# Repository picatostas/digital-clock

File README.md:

# digital-clock
Eagle files for my TTL-CMOS digital clock

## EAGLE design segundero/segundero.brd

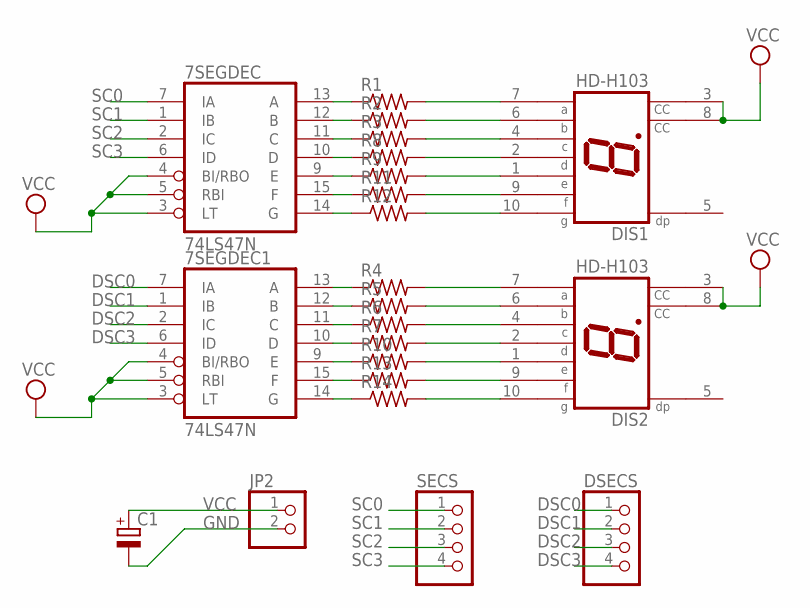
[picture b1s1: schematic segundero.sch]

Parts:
7SEGDEC, 7SEGDEC1: 74LS47N; DIL16
C1: CPOL-EUE2-5; E2-5
DIS1, DIS2: HD-H103; HDSP-M
DSECS: PINHD-1X4; 1X04
JP2: PINHD-1X2; 1X02
R1, R2, R3, R4, R5, R6, R7, R8, R9, R10, R11, R12, R13, R14: R-US_0204/7; 0204/7
SECS: PINHD-1X4; 1X04

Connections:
DSC0: 7SEGDEC1.7 (IA), DSECS.1
DSC1: 7SEGDEC1.1 (IB), DSECS.2
DSC2: 7SEGDEC1.2 (IC), DSECS.3
DSC3: 7SEGDEC1.6 (ID), DSECS.4
GND: 7SEGDEC.8 (GND), 7SEGDEC1.8 (GND), C1.-, JP2.2
unnamed: 7SEGDEC1.15 (F), R13.1
unnamed: 7SEGDEC1.13 (A), R4.1
unnamed: 7SEGDEC.15 (F), R11.1
unnamed: 7SEGDEC1.12 (B), R5.1
unnamed: 7SEGDEC.13 (A), R1.1
unnamed: 7SEGDEC1.11 (C), R6.1
unnamed: 7SEGDEC1.10 (D), R7.1
unnamed: 7SEGDEC1.9 (E), R10.1
unnamed: 7SEGDEC.12 (B), R2.1
unnamed: 7SEGDEC.11 (C), R3.1
unnamed: 7SEGDEC.10 (D), R8.1
unnamed: 7SEGDEC.9 (E), R9.1
unnamed: 7SEGDEC.14 (G), R12.1
unnamed: 7SEGDEC1.14 (G), R14.1
unnamed: DIS1.7 (A), R1.2
unnamed: DIS1.6 (B), R2.2
unnamed: DIS1.4 (C), R3.2
unnamed: DIS1.2 (D), R8.2
unnamed: DIS1.1 (E), R9.2
unnamed: DIS1.9 (F), R11.2
unnamed: DIS1.10 (G), R12.2
unnamed: DIS2.7 (A), R4.2
unnamed: DIS2.6 (B), R5.2
unnamed: DIS2.4 (C), R6.2
unnamed: DIS2.2 (D), R7.2
unnamed: DIS2.1 (E), R10.2
unnamed: DIS2.9 (F), R13.2
unnamed: DIS2.10 (G), R14.2
SC0: 7SEGDEC.7 (IA), SECS.1
SC1: 7SEGDEC.1 (IB), SECS.2
SC2: 7SEGDEC.2 (IC), SECS.3
SC3: 7SEGDEC.6 (ID), SECS.4
VCC: 7SEGDEC.3 (LT), 7SEGDEC.4 (BI/RBO), 7SEGDEC.5 (RBI), 7SEGDEC.16 (VCC), 7SEGDEC1.3 (LT), 7SEGDEC1.4 (BI/RBO), 7SEGDEC1.5 (RBI), 7SEGDEC1.16 (VCC), C1.+, DIS1.3 (CC), DIS1.8 (CC), DIS2.3 (CC), DIS2.8 (CC), JP2.1

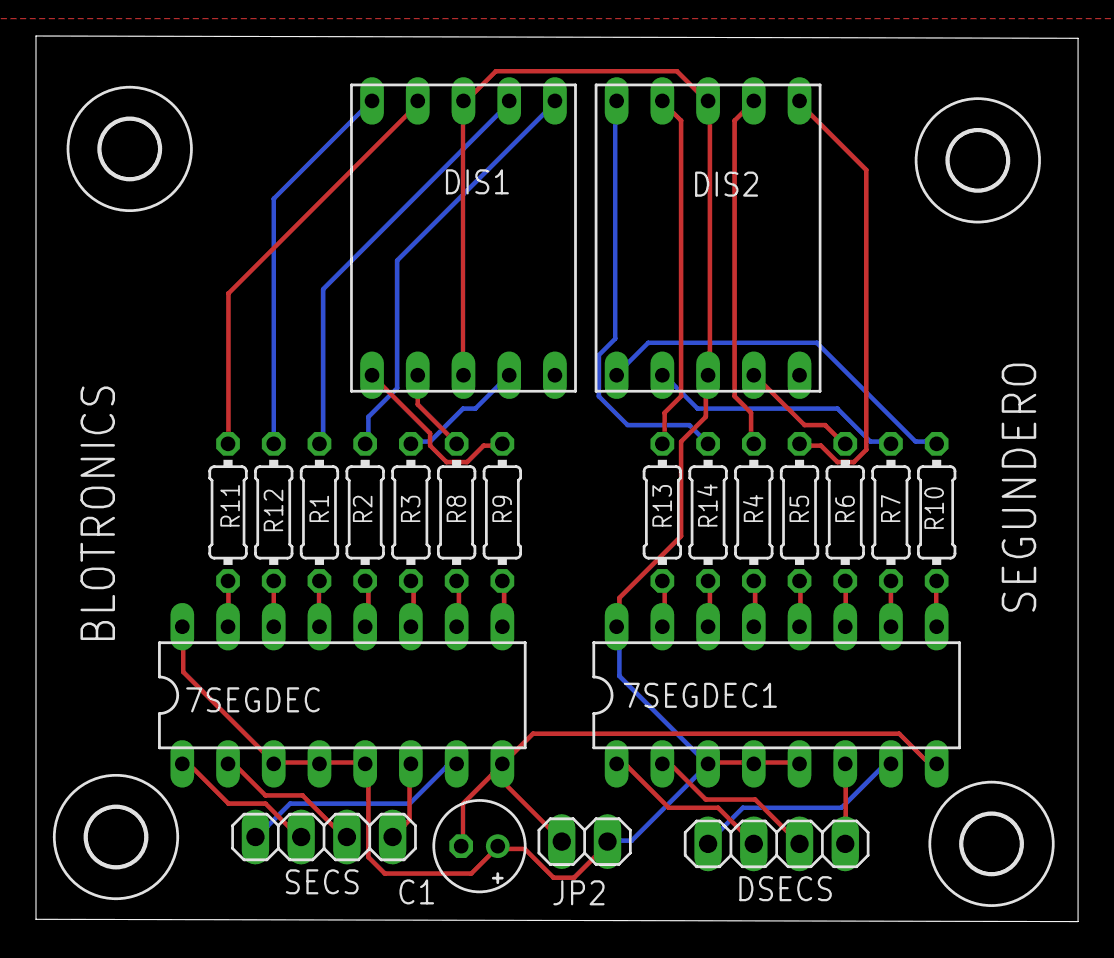
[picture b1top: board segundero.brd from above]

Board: 2 copper layers, 57.9 x 49.2 mm, 26 parts (0 on the bottom side), 38 nets.

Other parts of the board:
U$1, U$2, U$3, U$4: 3,2

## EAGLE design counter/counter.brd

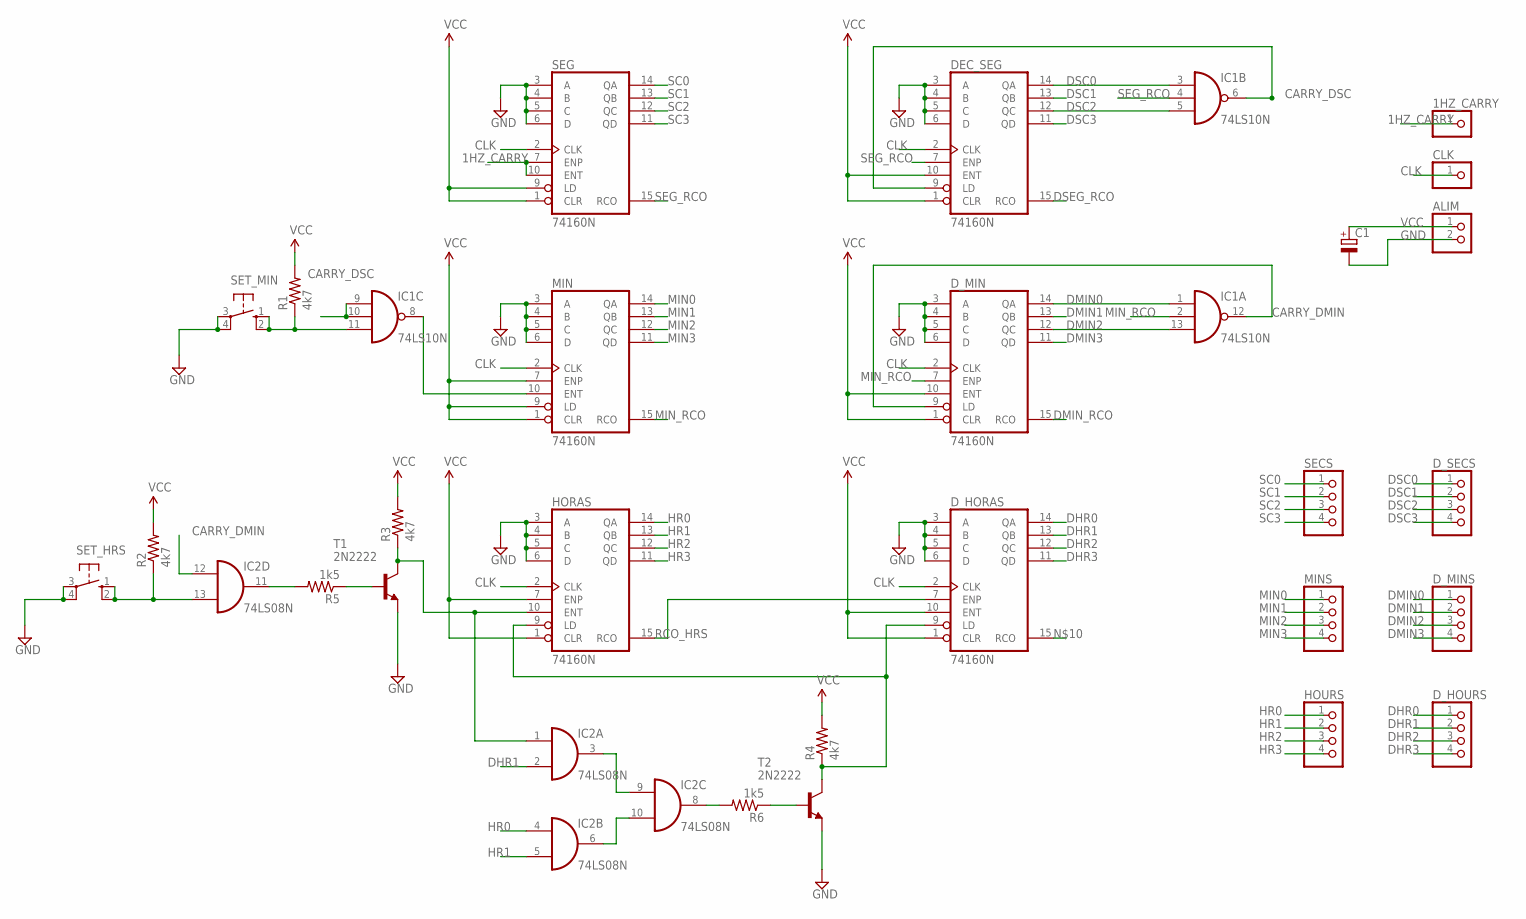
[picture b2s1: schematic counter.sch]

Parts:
1HZ_CARRY: PINHD-1X1; 1X01
ALIM: PINHD-1X2; 1X02
C1: CPOL-EUE2-5; E2-5
CLK: PINHD-1X1; 1X01
DEC_SEG: 74160N; DIL16
D_HORAS: 74160N; DIL16
D_HOURS: PINHD-1X4; 1X04
D_MIN: 74160N; DIL16
D_MINS: PINHD-1X4; 1X04
D_SECS: PINHD-1X4; 1X04
HORAS: 74160N; DIL16
HOURS: PINHD-1X4; 1X04
IC1: 74LS10N; DIL14
IC2: 74LS08N; DIL14
MIN: 74160N; DIL16
MINS: PINHD-1X4; 1X04
R1, R2, R3, R4: 4k7; 0204/7
R5, R6: 1k5; 0204/7
SECS: PINHD-1X4; 1X04
SEG: 74160N; DIL16
SET_HRS: 40-XX; B3F-40XX
SET_MIN: 40-XX; B3F-40XX
T1, T2: 2N2222; TO92-EBC-OVAL

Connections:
1HZ_CARRY: 1HZ_CARRY.1, SEG.7 (ENP), SEG.10 (ENT)
CARRY_DMIN: D_MIN.9 (LD), IC1.12 (O), IC2.12 (I0)
CARRY_DSC: DEC_SEG.9 (LD), IC1.6 (O), IC1.9 (I0), IC1.10 (I1)
CLK: CLK.1, DEC_SEG.2 (CLK), D_HORAS.2 (CLK), D_MIN.2 (CLK), HORAS.2 (CLK), MIN.2 (CLK), SEG.2 (CLK)
DHR0: D_HORAS.14 (QA), D_HOURS.1
DHR1: D_HORAS.13 (QB), D_HOURS.2, IC2.2 (I1)
DHR2: D_HORAS.12 (QC), D_HOURS.3
DHR3: D_HORAS.11 (QD), D_HOURS.4
DMIN0: D_MIN.14 (QA), D_MINS.1, IC1.1 (I0)
DMIN1: D_MIN.13 (QB), D_MINS.2
DMIN2: D_MIN.12 (QC), D_MINS.3, IC1.13 (I2)
DMIN3: D_MIN.11 (QD), D_MINS.4
DMIN_RCO: D_MIN.15 (RCO)
DSC0: DEC_SEG.14 (QA), D_SECS.1, IC1.3 (I0)
DSC1: DEC_SEG.13 (QB), D_SECS.2
DSC2: DEC_SEG.12 (QC), D_SECS.3, IC1.5 (I2)
DSC3: DEC_SEG.11 (QD), D_SECS.4
DSEG_RCO: DEC_SEG.15 (RCO)
GND: ALIM.2, C1.-, DEC_SEG.3 (A), DEC_SEG.4 (B), DEC_SEG.5 (C), DEC_SEG.6 (D), DEC_SEG.8 (GND), D_HORAS.3 (A), D_HORAS.4 (B), D_HORAS.5 (C), D_HORAS.6 (D), D_HORAS.8 (GND), D_MIN.3 (A), D_MIN.4 (B), D_MIN.5 (C), D_MIN.6 (D), D_MIN.8 (GND), HORAS.3 (A), HORAS.4 (B), HORAS.5 (C), HORAS.6 (D), HORAS.8 (GND), IC1.7 (GND), IC2.7 (GND), MIN.3 (A), MIN.4 (B), MIN.5 (C), MIN.6 (D), MIN.8 (GND), SEG.3 (A), SEG.4 (B), SEG.5 (C), SEG.6 (D), SEG.8 (GND), SET_HRS.3, SET_HRS.4 (P1), SET_MIN.3, SET_MIN.4 (P1), T1.E, T2.E
HR0: HORAS.14 (QA), HOURS.1, IC2.4 (I0)
HR1: HORAS.13 (QB), HOURS.2, IC2.5 (I1)
HR2: HORAS.12 (QC), HOURS.3
HR3: HORAS.11 (QD), HOURS.4
MIN0: MIN.14 (QA), MINS.1
MIN1: MIN.13 (QB), MINS.2
MIN2: MIN.12 (QC), MINS.3
MIN3: MIN.11 (QD), MINS.4
MIN_RCO: D_MIN.7 (ENP), IC1.2 (I1), MIN.15 (RCO)
unnamed: IC1.11 (I2), R1.1, SET_MIN.1 (S), SET_MIN.2 (S1)
unnamed: IC2.11 (O), R5.2
unnamed: R5.1, T1.B
unnamed: IC2.6 (O), IC2.10 (I1)
unnamed: IC2.13 (I1), R2.1, SET_HRS.1 (S), SET_HRS.2 (S1)
unnamed: IC2.3 (O), IC2.9 (I0)
unnamed: IC2.8 (O), R6.2
unnamed: IC1.8 (O), MIN.10 (ENT)
unnamed: HORAS.10 (ENT), IC2.1 (I0), R3.1, T1.C
unnamed: R6.1, T2.B
unnamed: D_HORAS.9 (LD), HORAS.9 (LD), R4.1, T2.C
RCO_HRS: D_HORAS.7 (ENP), HORAS.15 (RCO)
SC0: SECS.1, SEG.14 (QA)
SC1: SECS.2, SEG.13 (QB)
SC2: SECS.3, SEG.12 (QC)
SC3: SECS.4, SEG.11 (QD)
SEG_RCO: DEC_SEG.7 (ENP), IC1.4 (I1), SEG.15 (RCO)
VCC: ALIM.1, C1.+, DEC_SEG.1 (CLR), DEC_SEG.10 (ENT), DEC_SEG.16 (VCC), D_HORAS.1 (CLR), D_HORAS.10 (ENT), D_HORAS.16 (VCC), D_MIN.1 (CLR), D_MIN.10 (ENT), D_MIN.16 (VCC), HORAS.1 (CLR), HORAS.7 (ENP), HORAS.16 (VCC), IC1.14 (VCC), IC2.14 (VCC), MIN.1 (CLR), MIN.7 (ENP), MIN.9 (LD), MIN.16 (VCC), R1.2, R2.2, R3.2, R4.2, SEG.1 (CLR), SEG.9 (LD), SEG.16 (VCC)

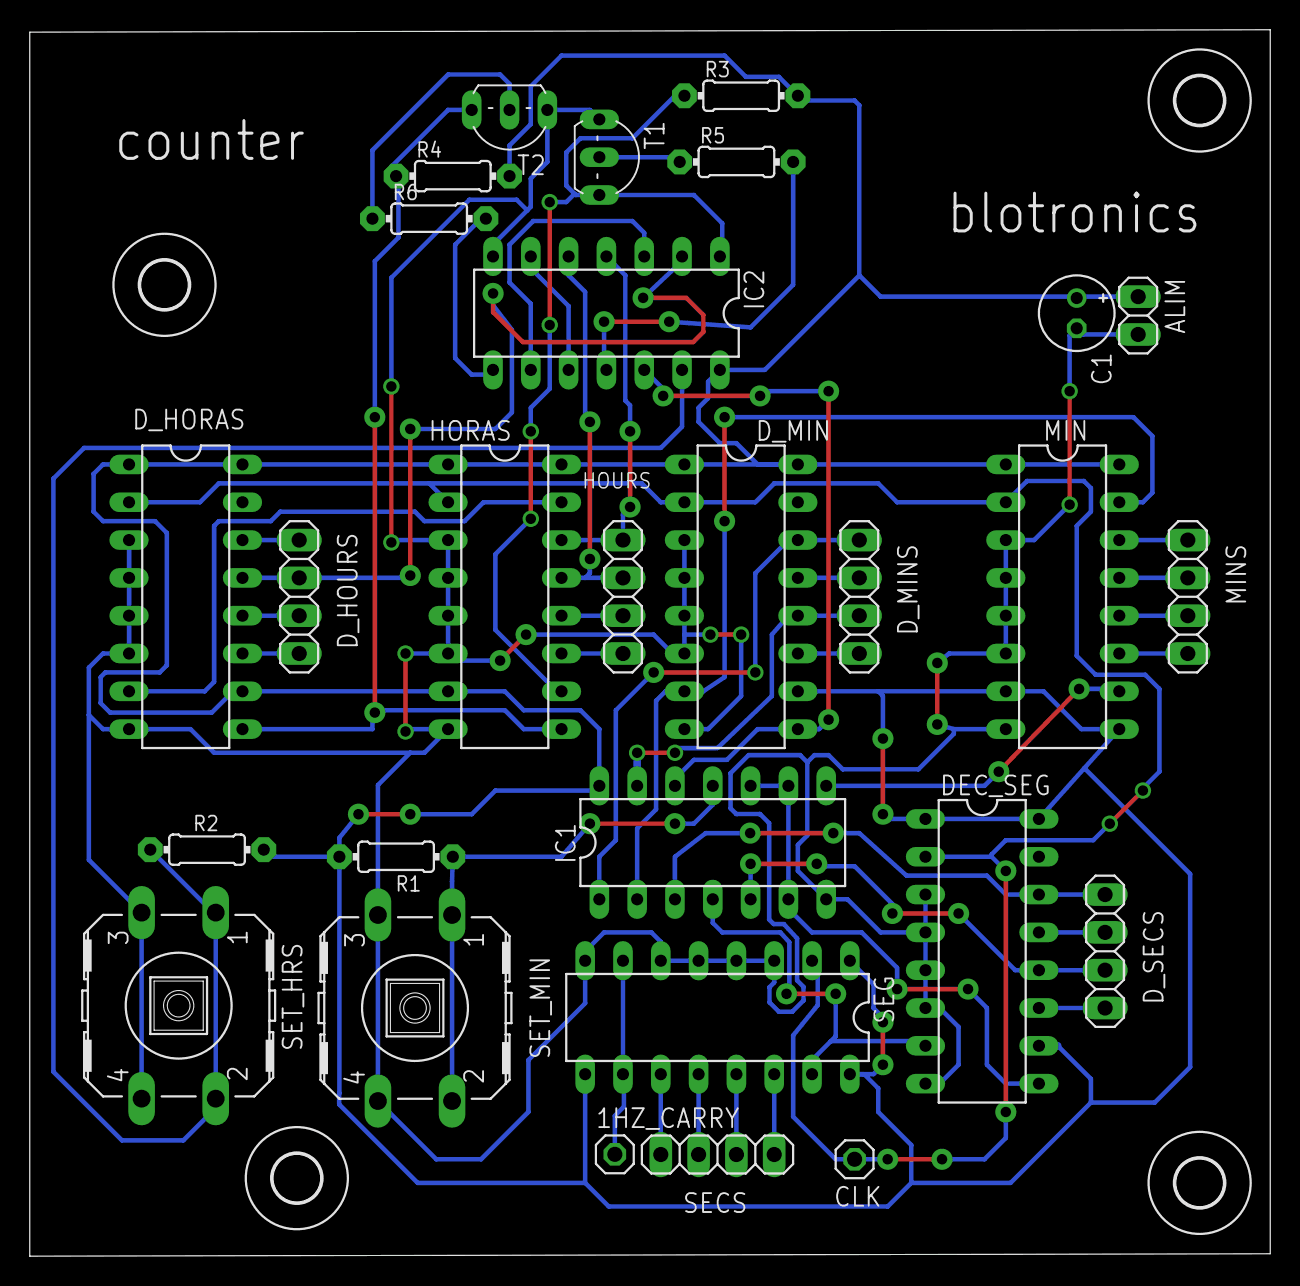
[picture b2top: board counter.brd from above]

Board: 2 copper layers, 83.3 x 82.4 mm, 32 parts (0 on the bottom side), 44 nets.

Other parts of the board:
U$1, U$2, U$3, U$4: 3,2

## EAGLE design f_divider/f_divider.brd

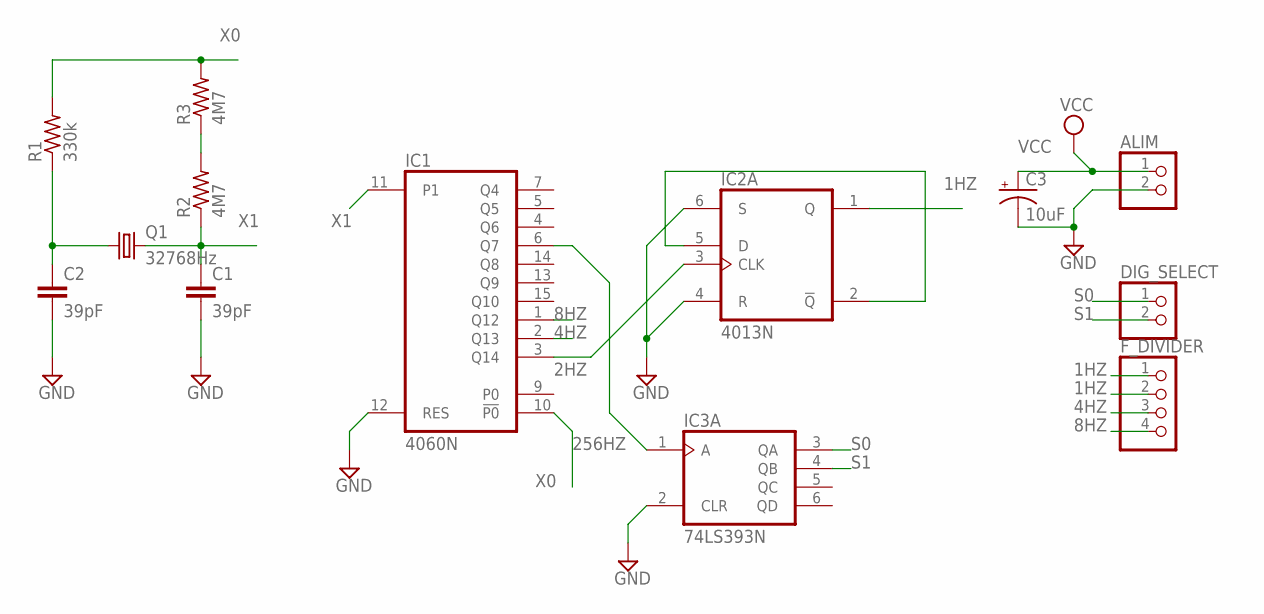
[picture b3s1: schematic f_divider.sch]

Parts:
ALIM: PINHD-1X2; 1X02
C1, C2: 39pF; CAP-PTH-SMALL-KIT
C3: 10uF; CPOL-RADIAL-10UF-25V
DIG_SELECT: PINHD-1X2; 1X02
F_DIVIDER: PINHD-1X4; 1X04
IC1: 4060N; DIL16
IC2: 4013N; DIL14
IC3: 74LS393N; DIL14
Q1: 32768Hz; TC26H
R1: 330k; 0204/7
R2, R3: 4M7; 0204/7

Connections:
1HZ: F_DIVIDER.1, F_DIVIDER.2, IC2.1 (Q)
2HZ: IC1.3 (Q14), IC2.3 (CLK)
4HZ: F_DIVIDER.3, IC1.2 (Q13)
8HZ: F_DIVIDER.4, IC1.1 (Q12)
256HZ: IC1.6 (Q7), IC3.1 (A)
GND: ALIM.2, C1.2, C2.2, C3.2 (-), IC1.8 (GND), IC1.12 (RES), IC2.4 (R), IC2.6 (S), IC2.7 (GND), IC3.2 (CLR), IC3.7 (GND)
unnamed: C2.1, Q1.1, R1.1
unnamed: R2.2, R3.1
unnamed: IC2.2 (!Q), IC2.5 (D)
S0: DIG_SELECT.1, IC3.3 (QA)
S1: DIG_SELECT.2, IC3.4 (QB)
VCC: ALIM.1, C3.1 (+), IC1.16 (VCC), IC2.14 (VCC), IC3.14 (VCC)
X0: IC1.10 (!P0), R1.2, R3.2
X1: C1.1, IC1.11 (P1), Q1.2, R2.1

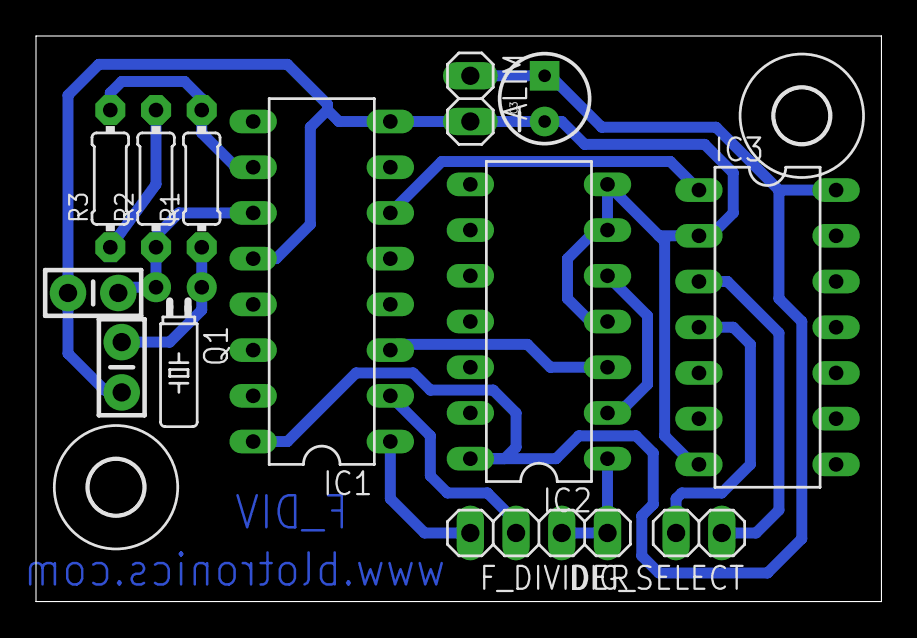
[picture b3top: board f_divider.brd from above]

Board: 2 copper layers, 47.0 x 31.4 mm, 15 parts (0 on the bottom side), 14 nets.

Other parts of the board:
U$1, U$2: 3,0

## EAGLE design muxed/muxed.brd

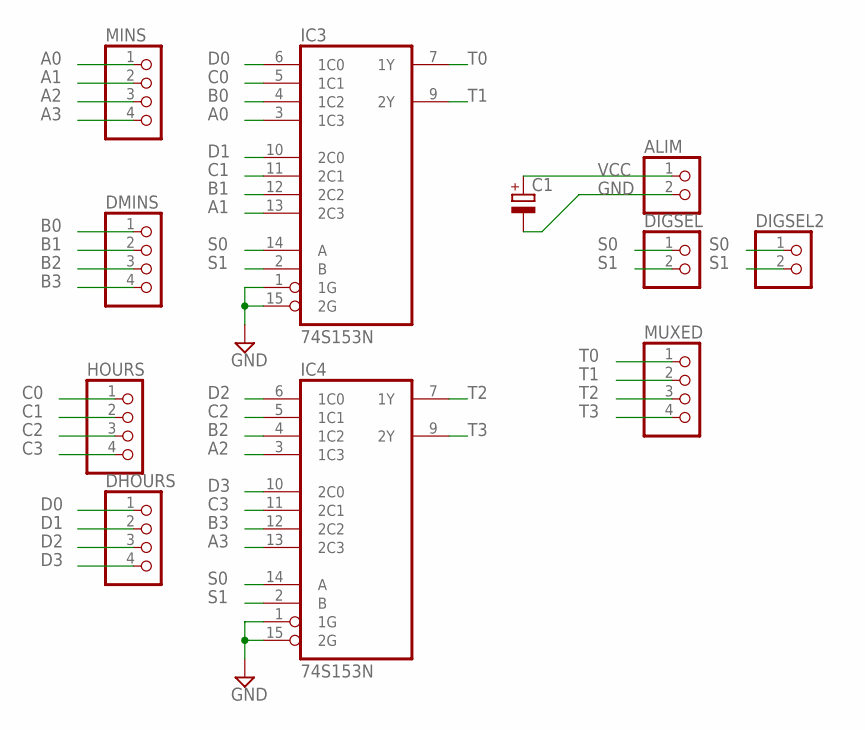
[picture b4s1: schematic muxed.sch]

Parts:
ALIM: PINHD-1X2; 1X02
C1: CPOL-EUE2-5; E2-5
DHOURS: PINHD-1X4; 1X04
DIGSEL, DIGSEL2: PINHD-1X2; 1X02
DMINS: PINHD-1X4; 1X04
HOURS: PINHD-1X4; 1X04
IC3, IC4: 74S153N; DIL16
MINS: PINHD-1X4; 1X04
MUXED: PINHD-1X4; 1X04

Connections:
A0: IC3.3 (1C3), MINS.1
A1: IC3.13 (2C3), MINS.2
A2: IC4.3 (1C3), MINS.3
A3: IC4.13 (2C3), MINS.4
B0: DMINS.1, IC3.4 (1C2)
B1: DMINS.2, IC3.12 (2C2)
B2: DMINS.3, IC4.4 (1C2)
B3: DMINS.4, IC4.12 (2C2)
C0: HOURS.1, IC3.5 (1C1)
C1: HOURS.2, IC3.11 (2C1)
C2: HOURS.3, IC4.5 (1C1)
C3: HOURS.4, IC4.11 (2C1)
D0: DHOURS.1, IC3.6 (1C0)
D1: DHOURS.2, IC3.10 (2C0)
D2: DHOURS.3, IC4.6 (1C0)
D3: DHOURS.4, IC4.10 (2C0)
GND: ALIM.2, C1.-, IC3.1 (1G), IC3.8 (GND), IC3.15 (2G), IC4.1 (1G), IC4.8 (GND), IC4.15 (2G)
S0: DIGSEL.1, DIGSEL2.1, IC3.14 (A), IC4.14 (A)
S1: DIGSEL.2, DIGSEL2.2, IC3.2 (B), IC4.2 (B)
T0: IC3.7 (1Y), MUXED.1
T1: IC3.9 (2Y), MUXED.2
T2: IC4.7 (1Y), MUXED.3
T3: IC4.9 (2Y), MUXED.4
VCC: ALIM.1, C1.+, IC3.16 (VCC), IC4.16 (VCC)

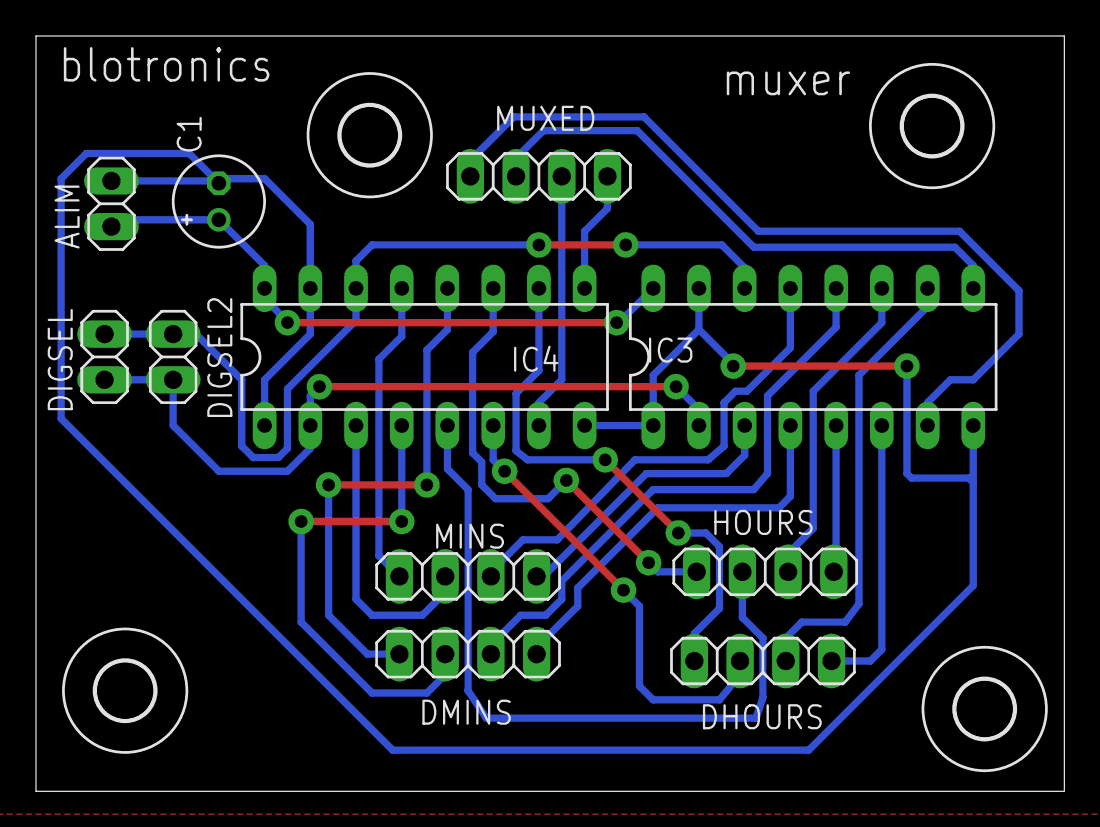
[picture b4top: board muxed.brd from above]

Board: 2 copper layers, 57.1 x 42.0 mm, 15 parts (0 on the bottom side), 24 nets.

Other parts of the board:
U$1, U$2, U$3, U$4: 3,2

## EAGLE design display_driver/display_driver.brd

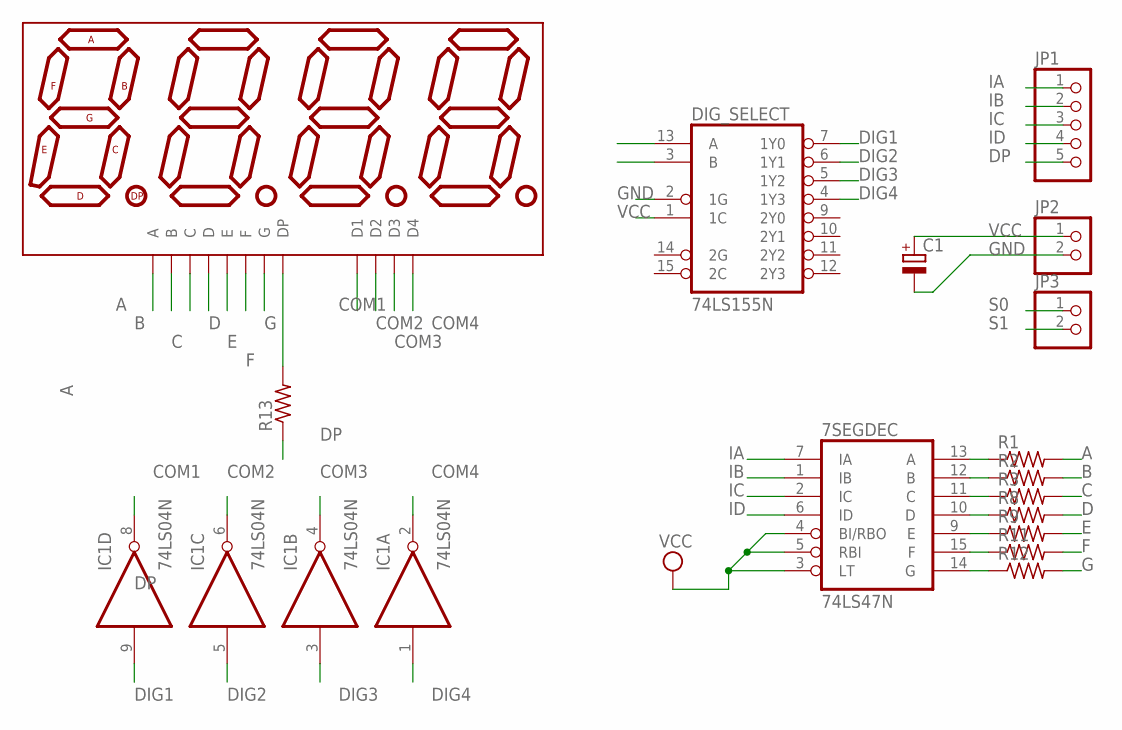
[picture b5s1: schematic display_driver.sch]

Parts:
7SEGDEC: 74LS47N; DIL16
C1: CPOL-EUE2-5; E2-5
DIG_SELECT: 74LS155N; DIL16
DISP1: 7-SEGMENT-4DIGIT-COUNTERCL5642BH-33; 4DIG_CA
IC1: 74LS04N; DIL14
JP1: PINHD-1X5; 1X05
JP2, JP3: PINHD-1X2; 1X02
R1, R2, R3, R8, R9, R11, R12, R13: R-US_0204/7; 0204/7

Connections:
A: DISP1.A, R1.2
B: DISP1.B, R2.2
C: DISP1.C, R3.2
COM1: DISP1.COM1 (D1), IC1.8 (O)
COM2: DISP1.COM2 (D2), IC1.6 (O)
COM3: DISP1.COM3 (D3), IC1.4 (O)
COM4: DISP1.COM4 (D4), IC1.2 (O)
D: DISP1.D, R8.2
DIG1: DIG_SELECT.7 (1Y0), IC1.9 (I)
DIG2: DIG_SELECT.6 (1Y1), IC1.5 (I)
DIG3: DIG_SELECT.5 (1Y2), IC1.3 (I)
DIG4: DIG_SELECT.4 (1Y3), IC1.1 (I)
DP: JP1.5, R13.1
E: DISP1.E, R9.2
F: DISP1.F, R11.2
G: DISP1.G, R12.2
GND: 7SEGDEC.8 (GND), C1.-, DIG_SELECT.2 (1G), DIG_SELECT.8 (GND), IC1.7 (GND), JP2.2
IA: 7SEGDEC.7 (IA), JP1.1
IB: 7SEGDEC.1 (IB), JP1.2
IC: 7SEGDEC.2 (IC), JP1.3
ID: 7SEGDEC.6 (ID), JP1.4
unnamed: 7SEGDEC.15 (F), R11.1
unnamed: DISP1.DP, R13.2
unnamed: 7SEGDEC.13 (A), R1.1
unnamed: 7SEGDEC.12 (B), R2.1
unnamed: 7SEGDEC.11 (C), R3.1
unnamed: 7SEGDEC.10 (D), R8.1
unnamed: 7SEGDEC.9 (E), R9.1
unnamed: 7SEGDEC.14 (G), R12.1
S0: DIG_SELECT.13 (A), JP3.1
S1: DIG_SELECT.3 (B), JP3.2
VCC: 7SEGDEC.3 (LT), 7SEGDEC.4 (BI/RBO), 7SEGDEC.5 (RBI), 7SEGDEC.16 (VCC), C1.+, DIG_SELECT.1 (1C), DIG_SELECT.16 (VCC), IC1.14 (VCC), JP2.1

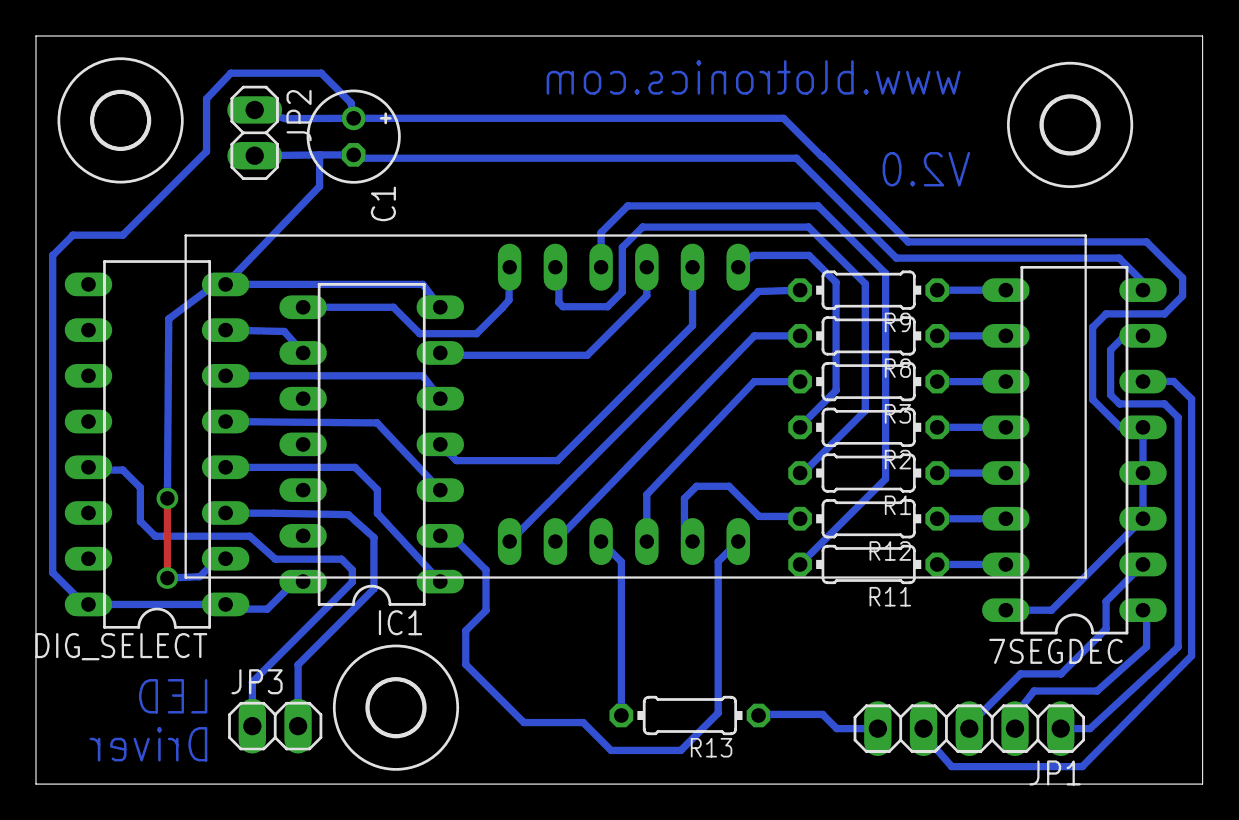
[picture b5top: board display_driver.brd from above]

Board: 2 copper layers, 64.8 x 41.6 mm, 19 parts (0 on the bottom side), 32 nets.

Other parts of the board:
U$1, U$2, U$3: 3,0

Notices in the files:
parts and their libraries:
SparkFun-Aesthetics: Licensing: Creative Commons ShareAlike 4.0 International - https://creativecommons.org/licenses/by-sa/4.0
